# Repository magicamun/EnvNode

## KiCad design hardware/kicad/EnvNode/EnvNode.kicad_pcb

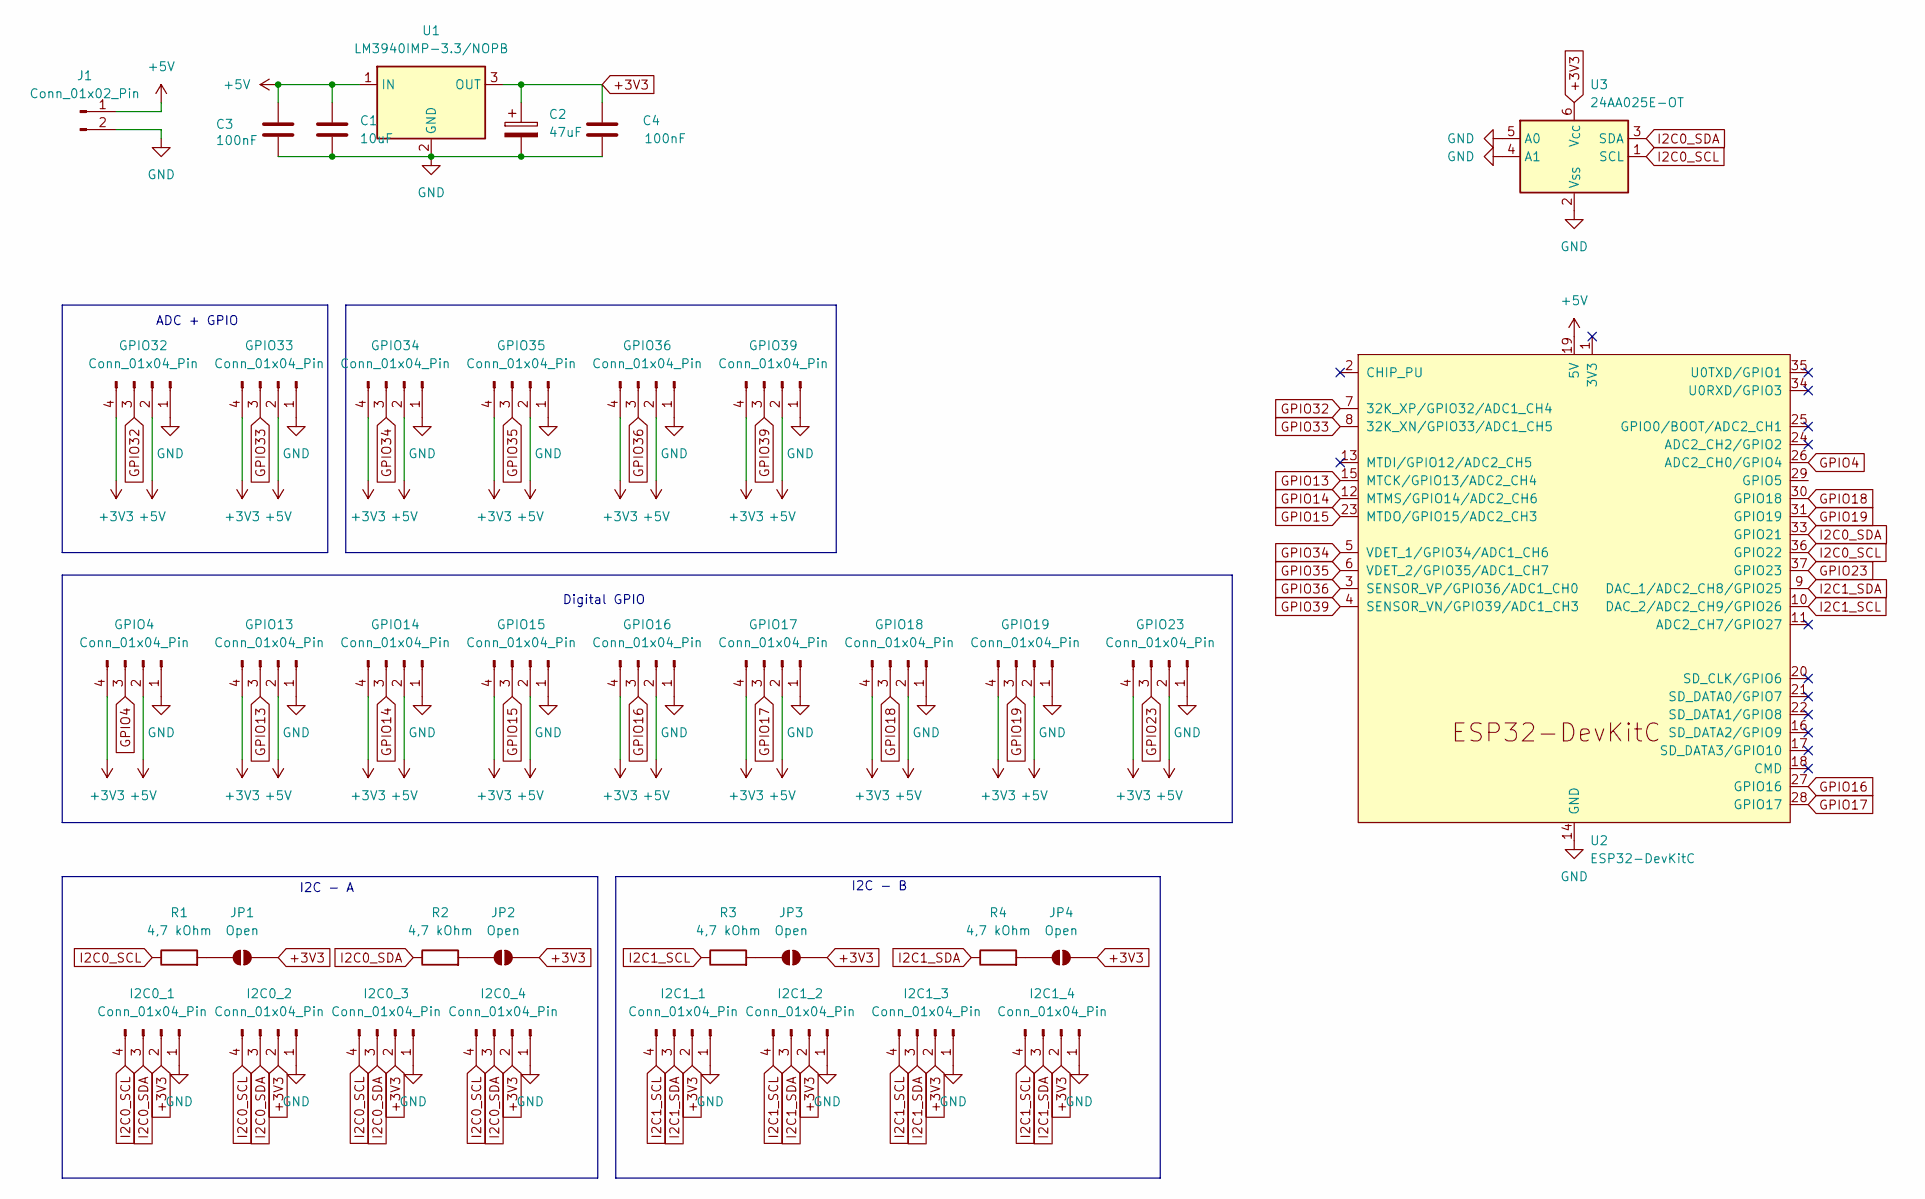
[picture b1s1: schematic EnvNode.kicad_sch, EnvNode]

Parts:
C1: 10uF; C_1206_3216Metric_Pad1.33x1.80mm_HandSolder
C2: 47uF; CP_EIA-3528-21_Kemet-B
C3, C4: 100nF; C_1206_3216Metric_Pad1.33x1.80mm_HandSolder
GPIO4, GPIO13, GPIO14, GPIO15, GPIO16, GPIO17, GPIO18, GPIO19, GPIO23, GPIO32, GPIO33, GPIO34, GPIO35, GPIO36, GPIO39: Conn_01x04_Pin; JST_PH_B4B-PH-K_1x04_P2.00mm_Vertical
I2C0_1, I2C0_2, I2C0_3, I2C1_1, I2C1_2, I2C1_3: Conn_01x04_Pin; JST_SH_SM04B-SRSS-TB_1x04-1MP_P1.00mm_Horizontal
I2C0_4, I2C1_4: Conn_01x04_Pin; QWIIC_PinSocket_1x04_P2.54mm_Vertical
J1: Conn_01x02_Pin; JST_PH_B2B-PH-K_1x02_P2.00mm_Vertical
JP1, JP2, JP3, JP4: Open; SolderJumper-2_P1.3mm_Open_Pad1.0x1.5mm
R1, R2, R3, R4: 4,7 kOhm; R_1206_3216Metric_Pad1.30x1.75mm_HandSolder
U1: LM3940IMP-3.3/NOPB; SOT-223-3_TabPin2
U2: ESP32-DevKitC
U3: 24AA025E-OT; SOT-23-6_Handsoldering

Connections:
+3V3: C2.1, C4.2, GPIO4.4, GPIO13.4, GPIO14.4, GPIO15.4, GPIO16.4, GPIO17.4, GPIO18.4, GPIO19.4, GPIO23.4, GPIO32.4, GPIO33.4, GPIO34.4, GPIO35.4, GPIO36.4, GPIO39.4, I2C0_1.2, I2C0_2.2, I2C0_3.2, I2C0_4.2, I2C1_1.2, I2C1_2.2, I2C1_3.2, I2C1_4.2, JP1.2 (B), JP2.2 (B), JP3.2 (B), JP4.2 (B), U1.3 (OUT), U3.6 (V_{CC})
+5V: C1.1, C3.2, GPIO4.2, GPIO13.2, GPIO14.2, GPIO15.2, GPIO16.2, GPIO17.2, GPIO18.2, GPIO19.2, GPIO23.2, GPIO32.2, GPIO33.2, GPIO34.2, GPIO35.2, GPIO36.2, GPIO39.2, J1.1, U1.1 (IN), U2.19 (5V)
GND: C1.2, C2.2, C3.1, C4.1, GPIO4.1, GPIO13.1, GPIO14.1, GPIO15.1, GPIO16.1, GPIO17.1, GPIO18.1, GPIO19.1, GPIO23.1, GPIO32.1, GPIO33.1, GPIO34.1, GPIO35.1, GPIO36.1, GPIO39.1, I2C0_1.1, I2C0_2.1, I2C0_3.1, I2C0_4.1, I2C1_1.1, I2C1_2.1, I2C1_3.1, I2C1_4.1, J1.2, U1.2 (GND), U2.14 (GND), U2.32 (GND), U2.38 (GND), U3.2 (V_{SS}), U3.4 (A1), U3.5 (A0)
GPIO4: GPIO4.3, U2.26 (ADC2_CH0/GPIO4)
GPIO13: GPIO13.3, U2.15 (MTCK/GPIO13/ADC2_CH4)
GPIO14: GPIO14.3, U2.12 (MTMS/GPIO14/ADC2_CH6)
GPIO15: GPIO15.3, U2.23 (MTDO/GPIO15/ADC2_CH3)
GPIO16: GPIO16.3, U2.27 (GPIO16)
GPIO17: GPIO17.3, U2.28 (GPIO17)
GPIO18: GPIO18.3, U2.30 (GPIO18)
GPIO19: GPIO19.3, U2.31 (GPIO19)
GPIO23: GPIO23.3, U2.37 (GPIO23)
GPIO32: GPIO32.3, U2.7 (32K_XP/GPIO32/ADC1_CH4)
GPIO33: GPIO33.3, U2.8 (32K_XN/GPIO33/ADC1_CH5)
GPIO34: GPIO34.3, U2.5 (VDET_1/GPIO34/ADC1_CH6)
GPIO35: GPIO35.3, U2.6 (VDET_2/GPIO35/ADC1_CH7)
GPIO36: GPIO36.3, U2.3 (SENSOR_VP/GPIO36/ADC1_CH0)
GPIO39: GPIO39.3, U2.4 (SENSOR_VN/GPIO39/ADC1_CH3)
I2C0_SCL: I2C0_1.4, I2C0_2.4, I2C0_3.4, I2C0_4.4, R1.1, U2.36 (GPIO22), U3.1 (SCL)
I2C0_SDA: I2C0_1.3, I2C0_2.3, I2C0_3.3, I2C0_4.3, R2.1, U2.33 (GPIO21), U3.3 (SDA)
I2C1_SCL: I2C1_1.4, I2C1_2.4, I2C1_3.4, I2C1_4.4, R3.1, U2.10 (DAC_2/ADC2_CH9/GPIO26)
I2C1_SDA: I2C1_1.3, I2C1_2.3, I2C1_3.3, I2C1_4.3, R4.1, U2.9 (DAC_1/ADC2_CH8/GPIO25)
unnamed: JP1.1 (A), R1.2
unnamed: JP2.1 (A), R2.2
unnamed: JP3.1 (A), R3.2
unnamed: JP4.1 (A), R4.2

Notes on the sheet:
ADC + GPIO
I2C - A
I2C - B
Digital GPIO

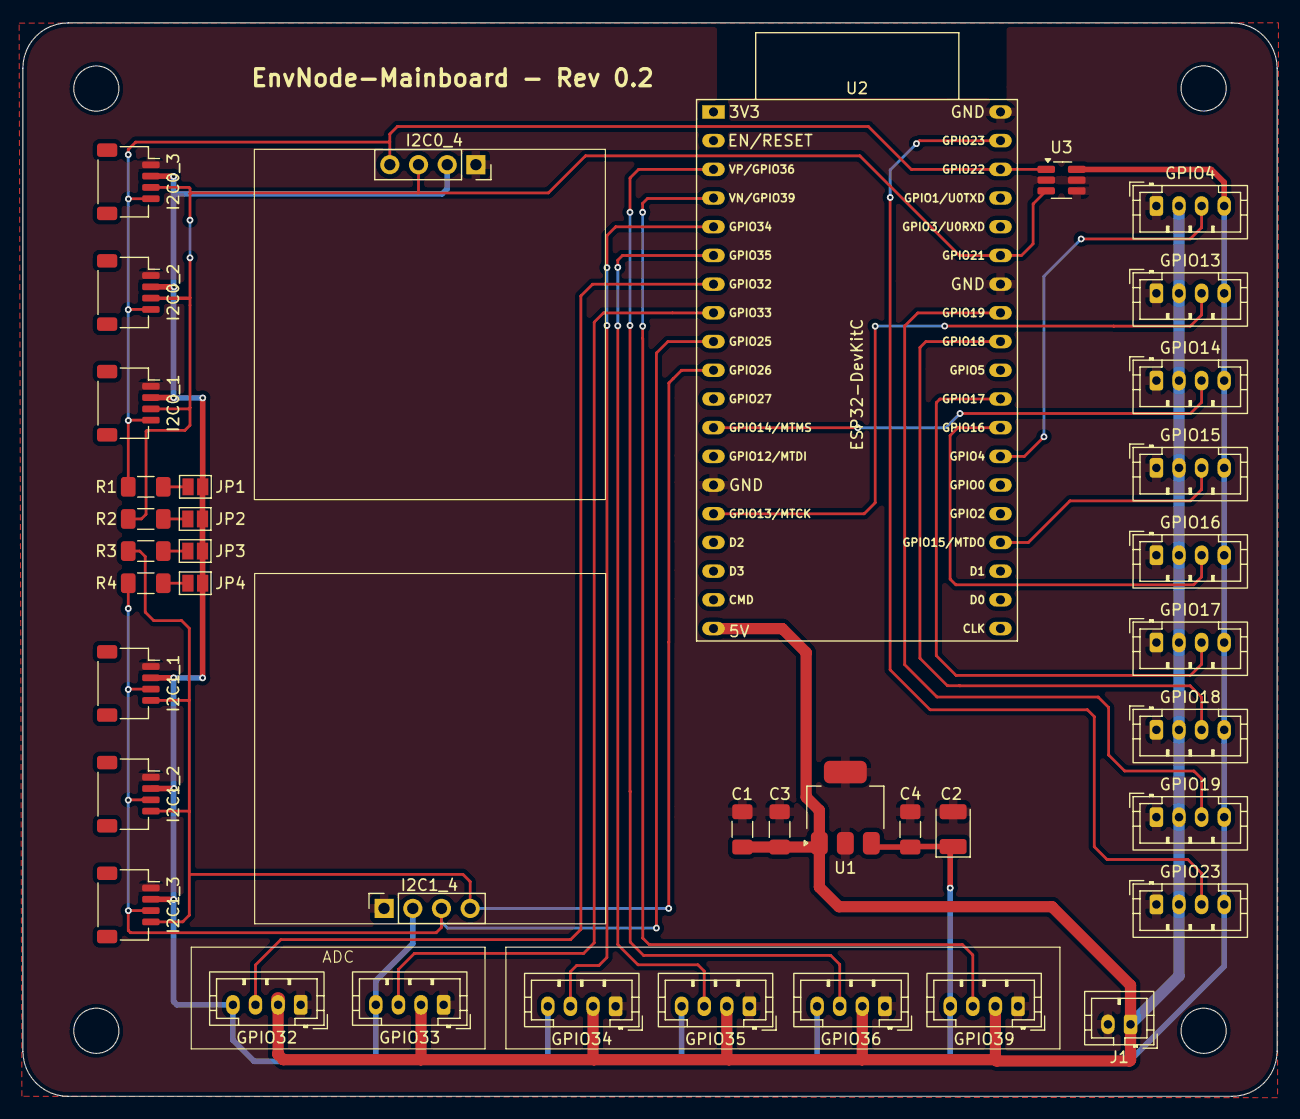
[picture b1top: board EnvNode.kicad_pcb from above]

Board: 2 copper layers, 111.0 x 95.0 mm, 39 parts (0 on the bottom side), 26 nets.

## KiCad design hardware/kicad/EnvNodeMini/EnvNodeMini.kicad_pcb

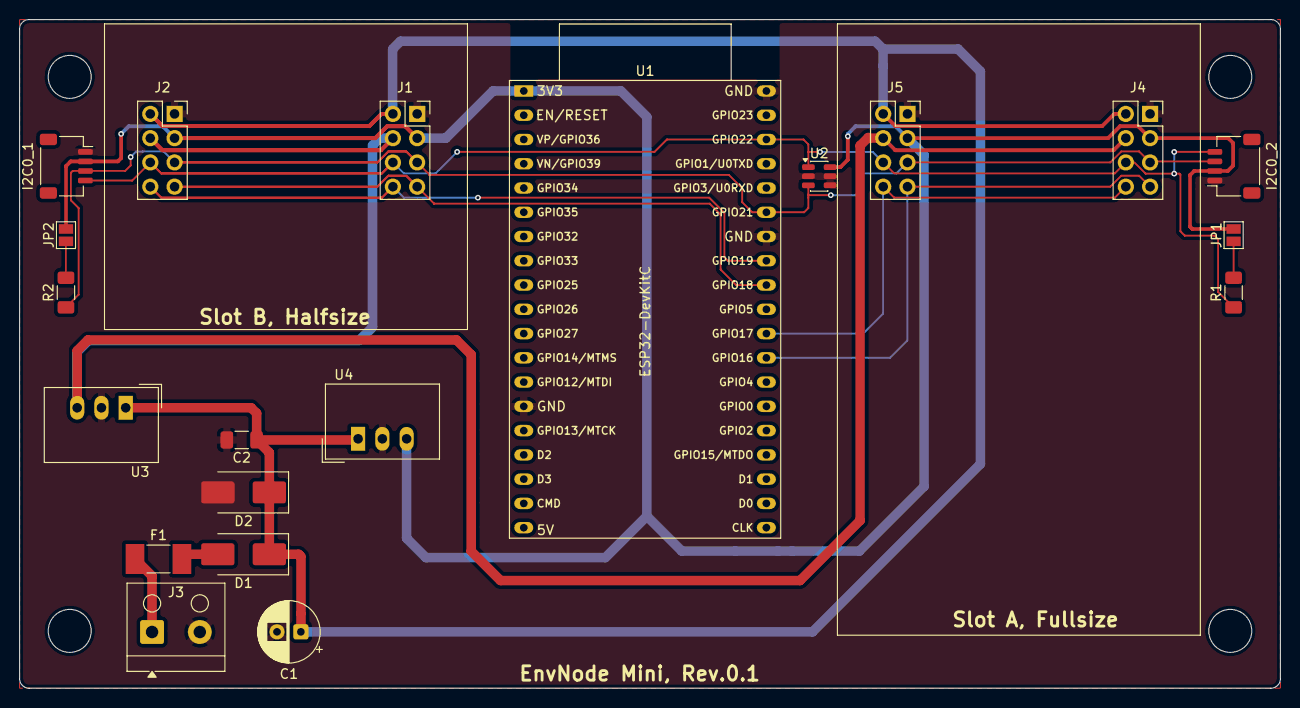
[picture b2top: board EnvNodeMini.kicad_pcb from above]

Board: 2 copper layers, 132.0 x 70.0 mm, 20 parts (0 on the bottom side), 14 nets.

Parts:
C1: 47uF/50V; CP_Radial_D6.3mm_P2.50mm
C2: 100nF / 50V X7R; C_1206_3216Metric_Pad1.33x1.80mm_HandSolder
D1: STPS3L60S; D_SMB_Handsoldering
D2: SMBJ24A; D_SMB_Handsoldering
F1: 2A; Fuse_Littelfuse-NANO2-451_453
I2C0_1, I2C0_2: Conn_01x04_Pin; JST_SH_SM04B-SRSS-TB_1x04-1MP_P1.00mm_Horizontal
J1, J2, J4, J5: Conn_02x04_Odd_Even; PinSocket_2x04_P2.54mm_Vertical
J3: Power; TerminalBlock_RND_205-00001_1x02_P5.00mm_Horizontal
JP1, JP2: Open; SolderJumper-2_P1.3mm_Open_Pad1.0x1.5mm
R1, R2: 4,7 kOhm; R_1206_3216Metric_Pad1.30x1.75mm_HandSolder
U1: ESP32-DevKitC
U2: 24AA025E-OT; SOT-23-6
U3: TSR_1-2450; Converter_DCDC_TRACO_TSR-1_THT
U4: TSR_1-2433; Converter_DCDC_TRACO_TSR-1_THT

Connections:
3V3: I2C0_1.2, I2C0_2.2, J1.3, J2.3, J4.3, J5.3, JP1.2 (B), JP2.2 (B), U1.1 (3V3), U2.6 (V_{CC}), U4.3 (Vout)
5V: J1.4, J2.4, J4.4, J5.4, U3.3 (Vout)
24V: C1.1, C2.1, D1.1 (K), D2.1 (K), J1.2, J2.2, J4.2, J5.2, U3.1 (Vin), U4.1 (Vin)
+24V_IN: F1.1, J3.1
GND: C1.2, C2.2, D2.2 (A), I2C0_1.1, I2C0_2.1, J1.1, J2.1, J3.2, J4.1, J5.1, U1.14 (GND), U1.32 (GND), U1.38 (GND), U2.2 (V_{SS}), U2.4 (A1), U2.5 (A0), U3.2 (GND), U4.2 (GND)
GPIO16: J4.7, J5.7, U1.27 (GPIO16)
GPIO17: J4.8, J5.8, U1.28 (GPIO17)
GPIO18: J1.7, J2.7, U1.30 (GPIO18)
GPIO19: J1.8, J2.8, U1.31 (GPIO19)
I2C0_SCL: I2C0_1.4, I2C0_2.4, J1.6, J2.6, J4.6, J5.6, R1.1, U1.36 (GPIO22), U2.1 (SCL)
I2C0_SDA: I2C0_1.3, I2C0_2.3, J1.5, J2.5, J4.5, J5.5, R2.1, U1.33 (GPIO21), U2.3 (SDA)
unnamed: D1.2 (A), F1.2
unnamed: JP1.1 (A), R1.2
unnamed: JP2.1 (A), R2.2

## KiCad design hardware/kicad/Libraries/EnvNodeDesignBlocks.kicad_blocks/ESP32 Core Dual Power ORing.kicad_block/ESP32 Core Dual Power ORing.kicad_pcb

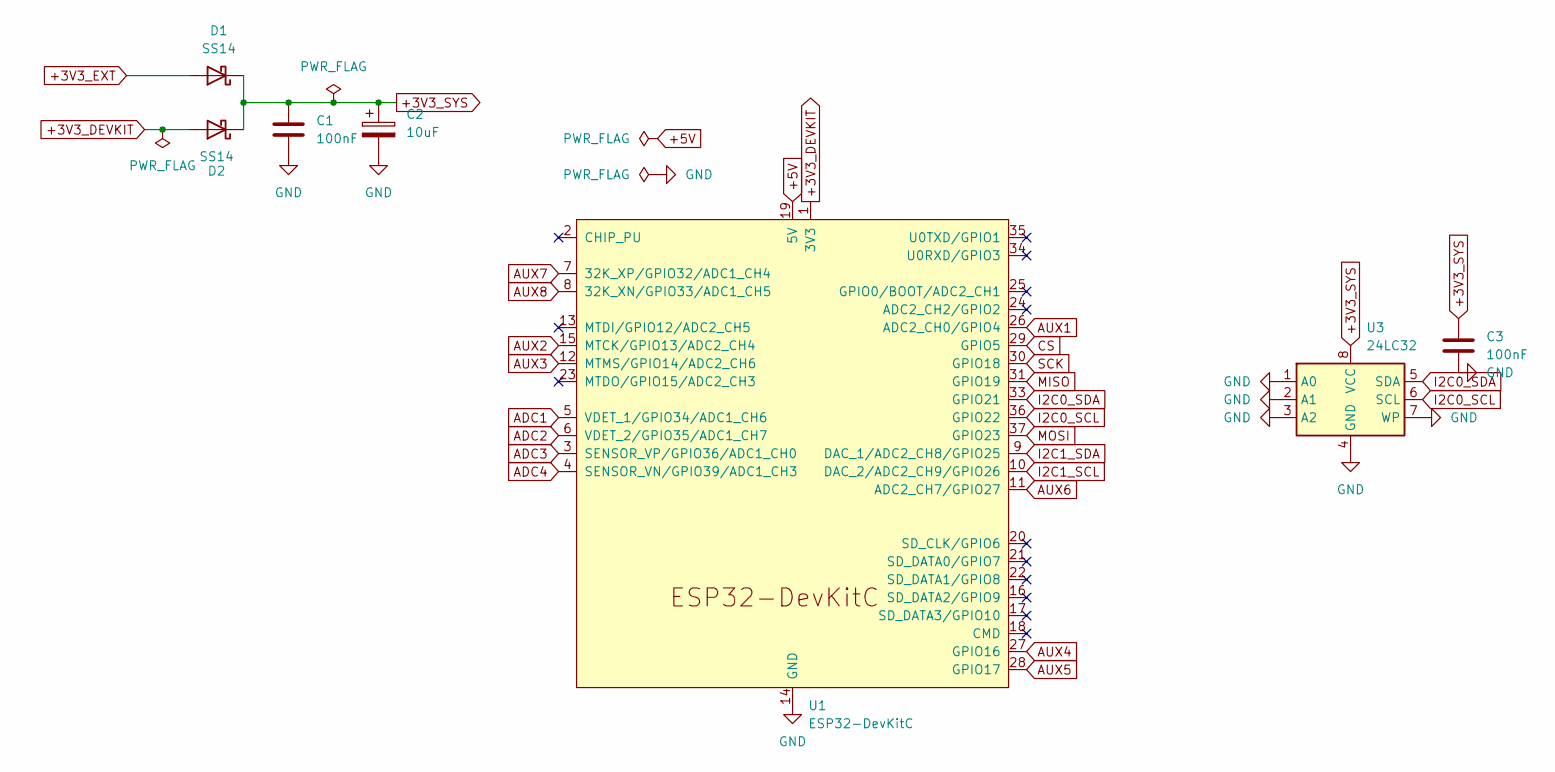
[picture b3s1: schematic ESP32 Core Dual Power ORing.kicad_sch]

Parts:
C1, C3: 100nF; C_1206_3216Metric_Pad1.33x1.80mm_HandSolder
C2: 10uF; CP_Elec_5x5.4
D1, D2: SS14; D_SMA
U1: ESP32-DevKitC
U3: 24LC32; SOIC-8_3.9x4.9mm_P1.27mm

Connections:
+3V3_DEVKIT: D2.2 (A), U1.1 (3V3)
+3V3_EXT: D1.2 (A)
+3V3_SYS: C1.1, C2.1, C3.1, D1.1 (K), D2.1 (K), U3.8 (VCC)
+5V: U1.19 (5V)
ADC1: U1.5 (VDET_1/GPIO34/ADC1_CH6)
ADC2: U1.6 (VDET_2/GPIO35/ADC1_CH7)
ADC3: U1.3 (SENSOR_VP/GPIO36/ADC1_CH0)
ADC4: U1.4 (SENSOR_VN/GPIO39/ADC1_CH3)
AUX1: U1.26 (ADC2_CH0/GPIO4)
AUX2: U1.15 (MTCK/GPIO13/ADC2_CH4)
AUX3: U1.12 (MTMS/GPIO14/ADC2_CH6)
AUX4: U1.27 (GPIO16)
AUX5: U1.28 (GPIO17)
AUX6: U1.11 (ADC2_CH7/GPIO27)
AUX7: U1.7 (32K_XP/GPIO32/ADC1_CH4)
AUX8: U1.8 (32K_XN/GPIO33/ADC1_CH5)
CS: U1.29 (GPIO5)
GND: C1.2, C2.2, C3.2, U1.14 (GND), U1.32 (GND), U1.38 (GND), U3.1 (A0), U3.2 (A1), U3.3 (A2), U3.4 (GND), U3.7 (WP)
I2C0_SCL: U1.36 (GPIO22), U3.6 (SCL)
I2C0_SDA: U1.33 (GPIO21), U3.5 (SDA)
I2C1_SCL: U1.10 (DAC_2/ADC2_CH9/GPIO26)
I2C1_SDA: U1.9 (DAC_1/ADC2_CH8/GPIO25)
MISO: U1.31 (GPIO19)
MOSI: U1.37 (GPIO23)
SCK: U1.30 (GPIO18)

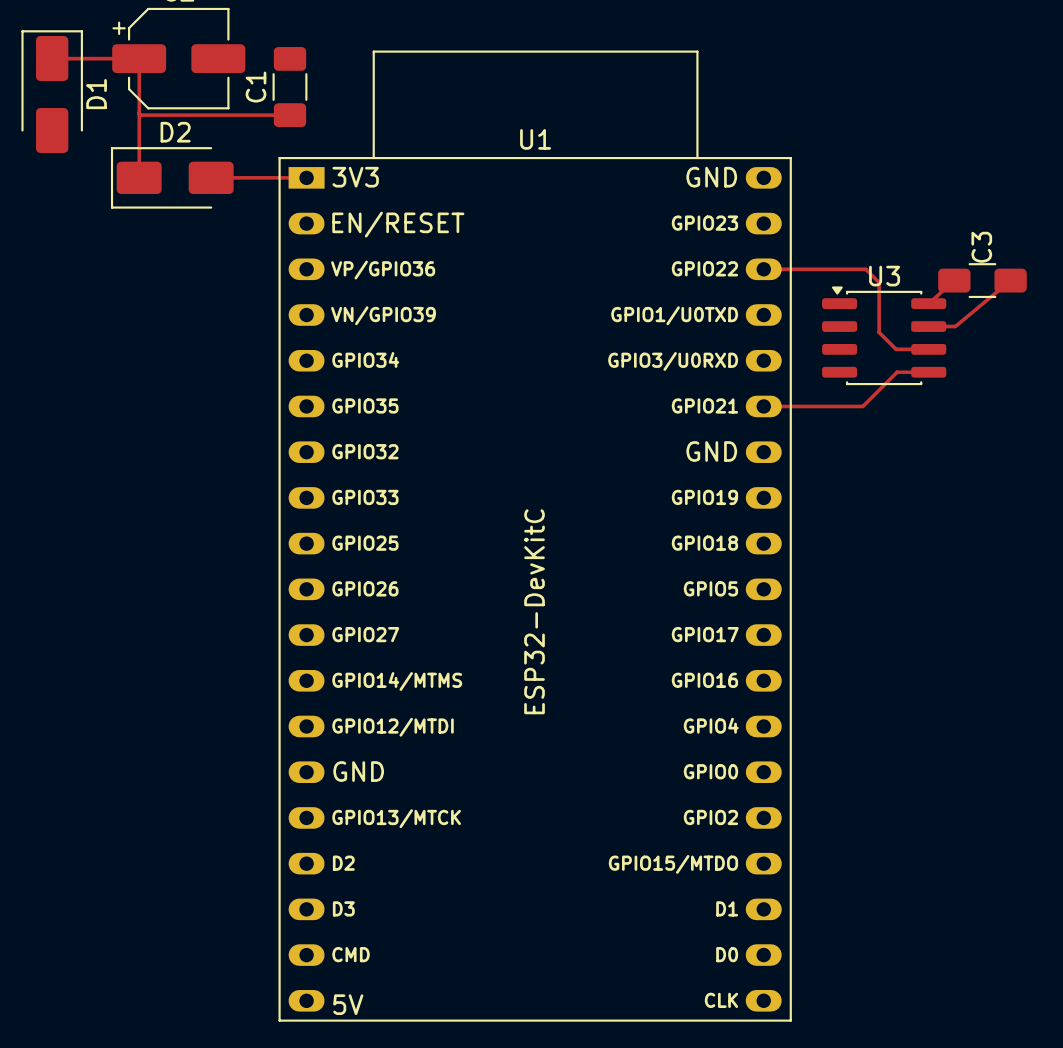
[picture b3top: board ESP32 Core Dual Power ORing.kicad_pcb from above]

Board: 2 copper layers, 7 parts (0 on the bottom side), 5 nets.

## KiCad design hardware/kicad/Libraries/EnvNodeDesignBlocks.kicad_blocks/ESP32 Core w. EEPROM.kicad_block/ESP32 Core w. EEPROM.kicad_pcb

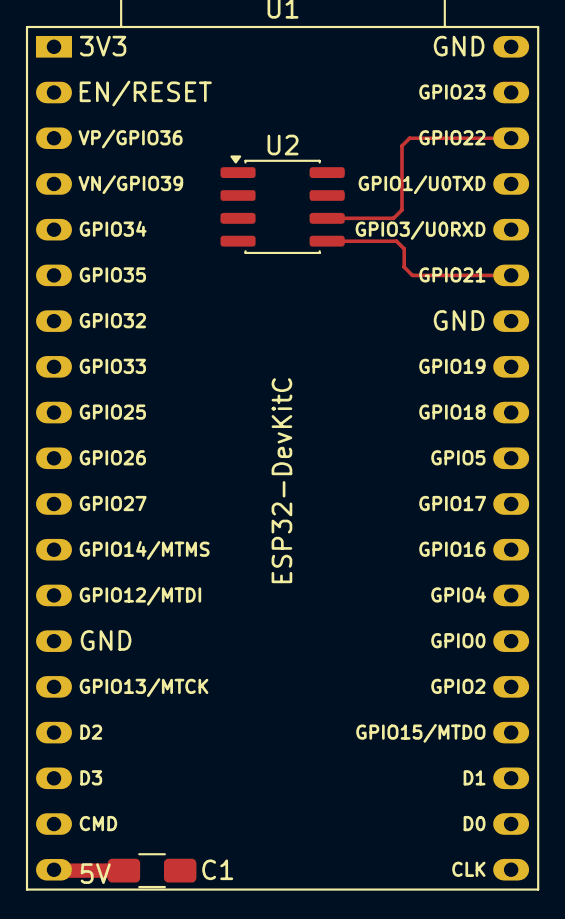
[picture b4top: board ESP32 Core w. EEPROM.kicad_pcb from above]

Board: 2 copper layers, 3 parts (0 on the bottom side), 4 nets.

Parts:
C1: 100nF; C_1206_3216Metric_Pad1.33x1.80mm_HandSolder
U1: ESP32-DevKitC
U2: 24LC32; SOIC-8_3.9x4.9mm_P1.27mm

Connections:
+5V: C1.1, U1.19 (5V)
GND: C1.2, U1.14 (GND), U1.32 (GND), U1.38 (GND), U2.1 (A0), U2.2 (A1), U2.3 (A2), U2.4 (GND), U2.7 (WP)
I2C0_SCL: U1.36 (GPIO22), U2.6 (SCL)
I2C0_SDA: U1.33 (GPIO21), U2.5 (SDA)
